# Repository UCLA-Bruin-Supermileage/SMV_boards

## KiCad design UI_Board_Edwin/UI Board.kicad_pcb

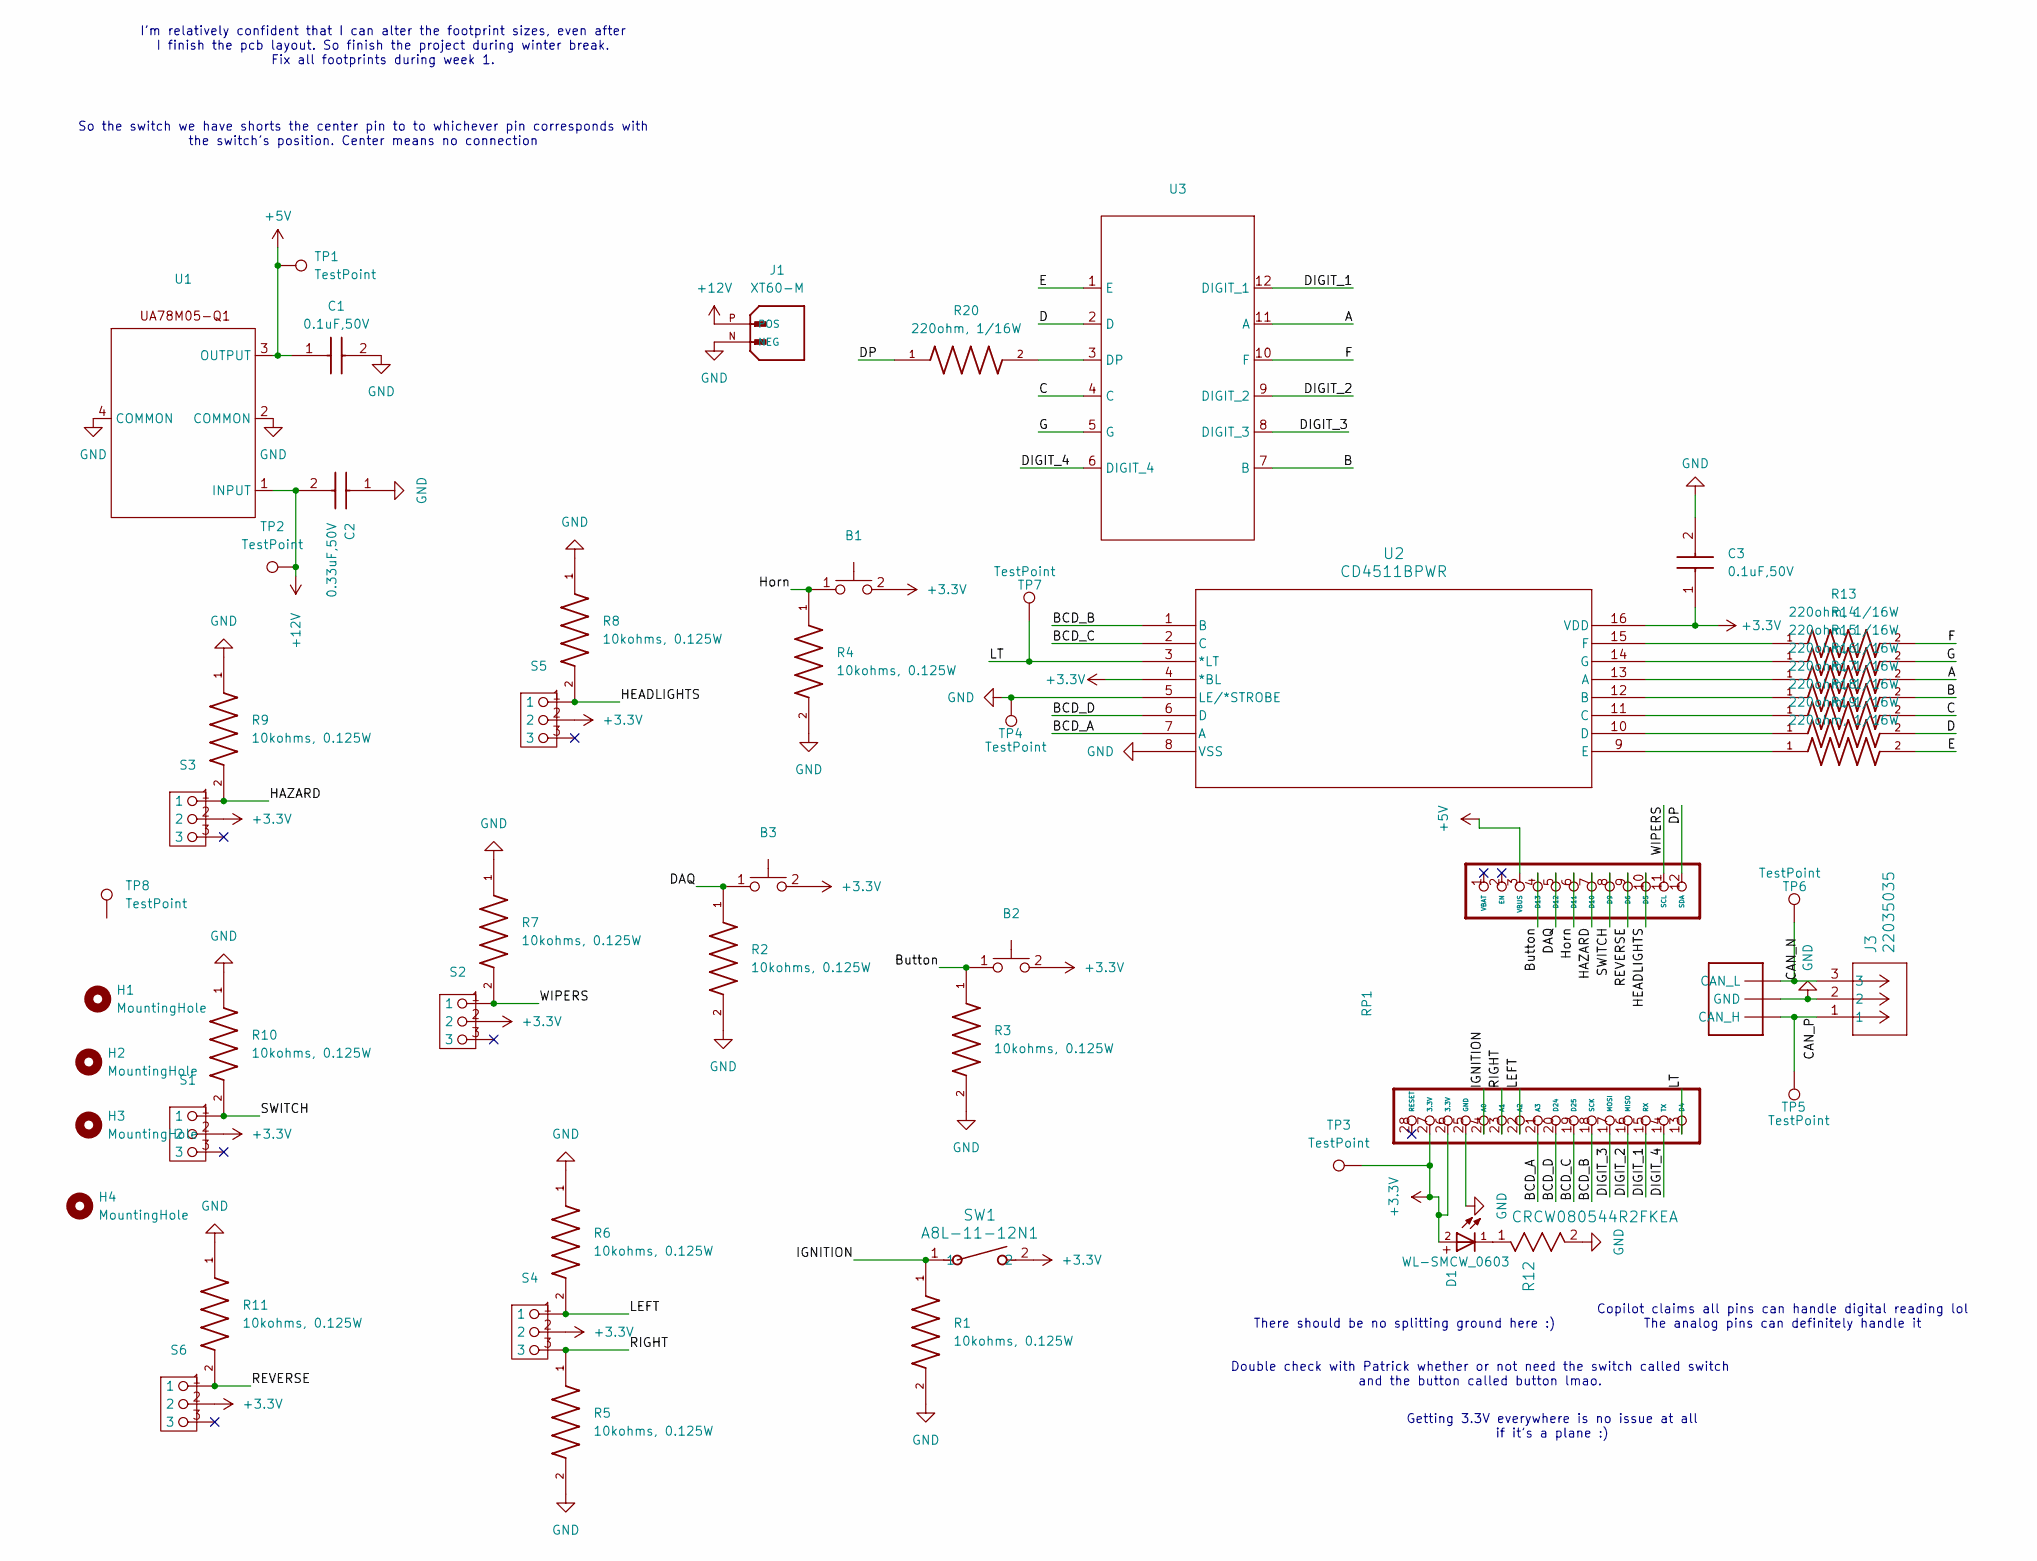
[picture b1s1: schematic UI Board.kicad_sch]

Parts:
B1, B2, B3: Twidec Button
C1, C3: 0.1uF,50V; Cap0805; Manufacturer_Part_Number C0805C104K5RACTU; Mouser Part Number 80-C0805C104K5R
C2: 0.33uF,50V; Cap0805; Manufacturer_Part_Number C0805C334K5RACTU; Mouser Part Number 80-C0805C334K5R
D1: WL-SMCW_0603; WL-SMCW_0603(diode)
H1, H2, H3, H4: MountingHole; MountingHole_3.2mm_M3
J1: XT60-M; AMASS_XT60-M; PARTREV V1.2
J3: 22035035; 3pin_CON_22035035_MOL
R1, R2, R3, R4, R5, R6, R7, R8, R9, R10, R11: 10kohms, 0.125W; 0805RESC2012X60N
R12: CRCW080544R2FKEA; 0805RESC2012X60N
R13, R14, R15, R16, R17, R18, R19, R20: 220ohm, 1/16W; RESC1005X35N
RP1: RP2040
S1, S2, S3, S4, S5, S6: Switches
SW1: A8L-11-12N1; SW_A8L-11_OMR
TP1, TP2, TP3, TP4, TP5, TP6, TP7: TestPoint; TestPoint_Pad_2.5x2.5mm
TP8: TestPoint; SEM_logo
U1: DCY4_TEX
U2: CD4511BPWR
U3: Seven_Seg_display

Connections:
+3.3V: B1.2, B2.2, B3.2, C3.1, D1.2, RP1.26 (3.3V), RP1.27 (3.3V), S1.2, S2.2, S3.2, S4.2, S5.2, S6.2, SW1.2, TP3.1, U2.4 (*BL), U2.16 (VDD)
+5V: C1.1, RP1.3 (VBUS), TP1.1, U1.3 (OUTPUT)
+12V: C2.2, J1.P (POS), TP2.1, U1.1 (INPUT)
/A: R15.2, U3.11 (A)
/B: R16.2, U3.7 (B)
/BCD_A: RP1.21 (A3), U2.7 (A)
/BCD_B: RP1.18 (SCK), U2.1 (B)
/BCD_C: RP1.19 (D25), U2.2 (C)
/BCD_D: RP1.20 (D24), U2.6 (D)
/Button: B2.1, R3.1, RP1.4 (D13)
/C: R17.2, U3.4 (C)
/CAN_N: J3.3, RP1.29 (CAN_L), TP6.1
/CAN_P: J3.1, RP1.31 (CAN_H), TP5.1
/D: R18.2, U3.2 (D)
/DAQ: B3.1, R2.1, RP1.5 (D12)
/DIGIT_1: RP1.15 (RX), U3.12 (DIGIT_1)
/DIGIT_2: RP1.16 (MISO), U3.9 (DIGIT_2)
/DIGIT_3: RP1.17 (MOSI), U3.8 (DIGIT_3)
/DIGIT_4: RP1.14 (TX), U3.6 (DIGIT_4)
/DP: R20.1, RP1.12 (SDA)
/E: R19.2, U3.1 (E)
/F: R13.2, U3.10 (F)
/G: R14.2, U3.5 (G)
/HAZARD: R9.2, RP1.7 (D10), S3.1
/HEADLIGHTS: R8.2, RP1.10 (D5), S5.1
/Horn: B1.1, R4.1, RP1.6 (D11)
/IGNITION: R1.1, RP1.24 (A0), SW1.1
/LEFT: R6.2, RP1.22 (A2), S4.1
/LT: RP1.13 (D4), TP7.1, U2.3 (*LT)
/REVERSE: R11.2, RP1.9 (D6), S6.1
/RIGHT: R5.1, RP1.23 (A1), S4.3
/SWITCH: R10.2, RP1.8 (D9), S1.1
/WIPERS: R7.2, RP1.11 (SCL), S2.1
GND: C1.2, C2.1, C3.2, J1.N (NEG), J3.2, R1.2, R2.2, R3.2, R4.2, R5.2, R6.1, R7.1, R8.1, R9.1, R10.1, R11.1, R12.2, RP1.25 (GND), RP1.30 (GND), TP4.1, U1.2 (COMMON), U1.4 (COMMON), U2.5 (LE/*STROBE), U2.8 (VSS)
unnamed: D1.1, R12.1
unnamed: R15.1, U2.13 (A)
unnamed: R16.1, U2.12 (B)
unnamed: R17.1, U2.11 (C)
unnamed: R18.1, U2.10 (D)
unnamed: R19.1, U2.9 (E)
unnamed: R13.1, U2.15 (F)
unnamed: R14.1, U2.14 (G)
unnamed: R20.2, U3.3 (DP)

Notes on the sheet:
Getting 3.3V everywhere is no issue at all if it's a plane :)
I'm relatively confident that I can alter the footprint sizes, even after I finish the pcb layout. So finish the project during winter break. Fix all footprints during week 1.
There should be no splitting ground here :)
Copilot claims all pins can handle digital reading lol The analog pins can definitely handle it
Double check with Patrick whether or not need the switch called switch and the button called button lmao.
So the switch we have shorts the center pin to to whichever pin corresponds with the switch's position. Center means no connection

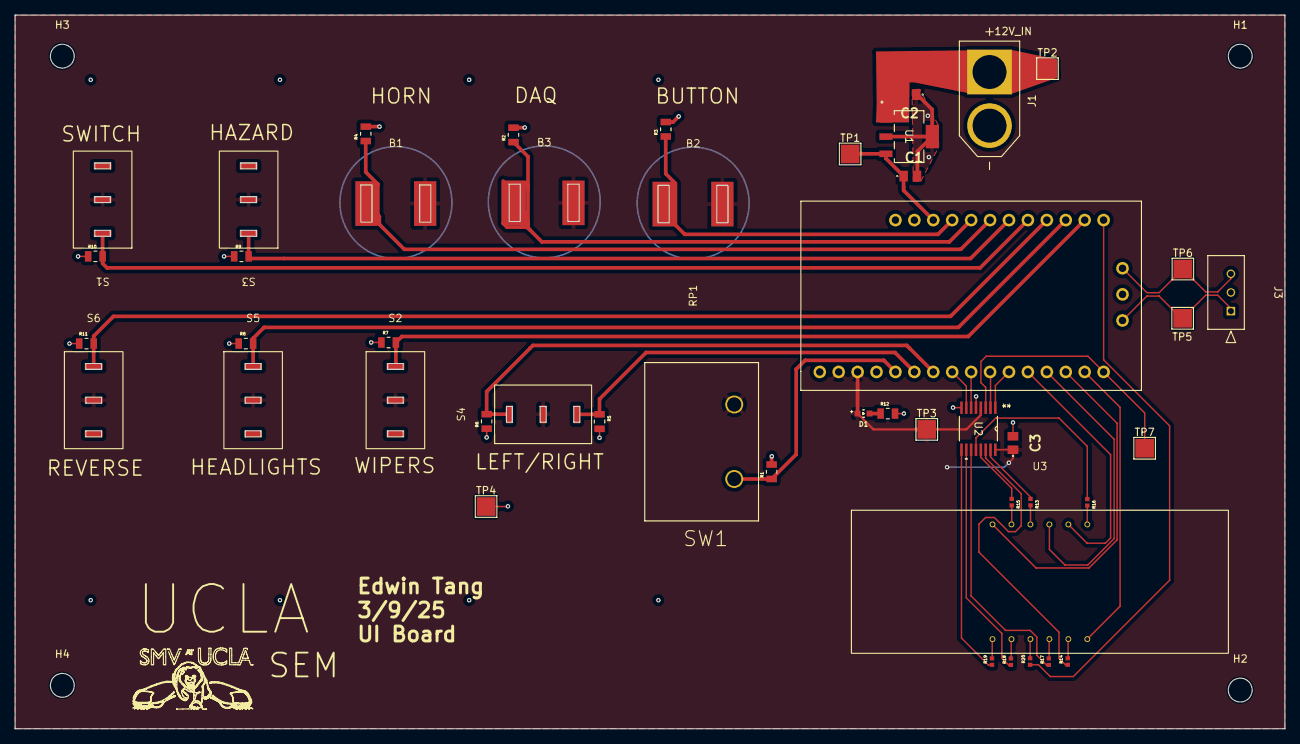
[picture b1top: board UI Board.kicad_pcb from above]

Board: 2 copper layers, 170.4 x 95.8 mm, 53 parts (0 on the bottom side), 43 nets.

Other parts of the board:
U1#2: UA78M05-Q1

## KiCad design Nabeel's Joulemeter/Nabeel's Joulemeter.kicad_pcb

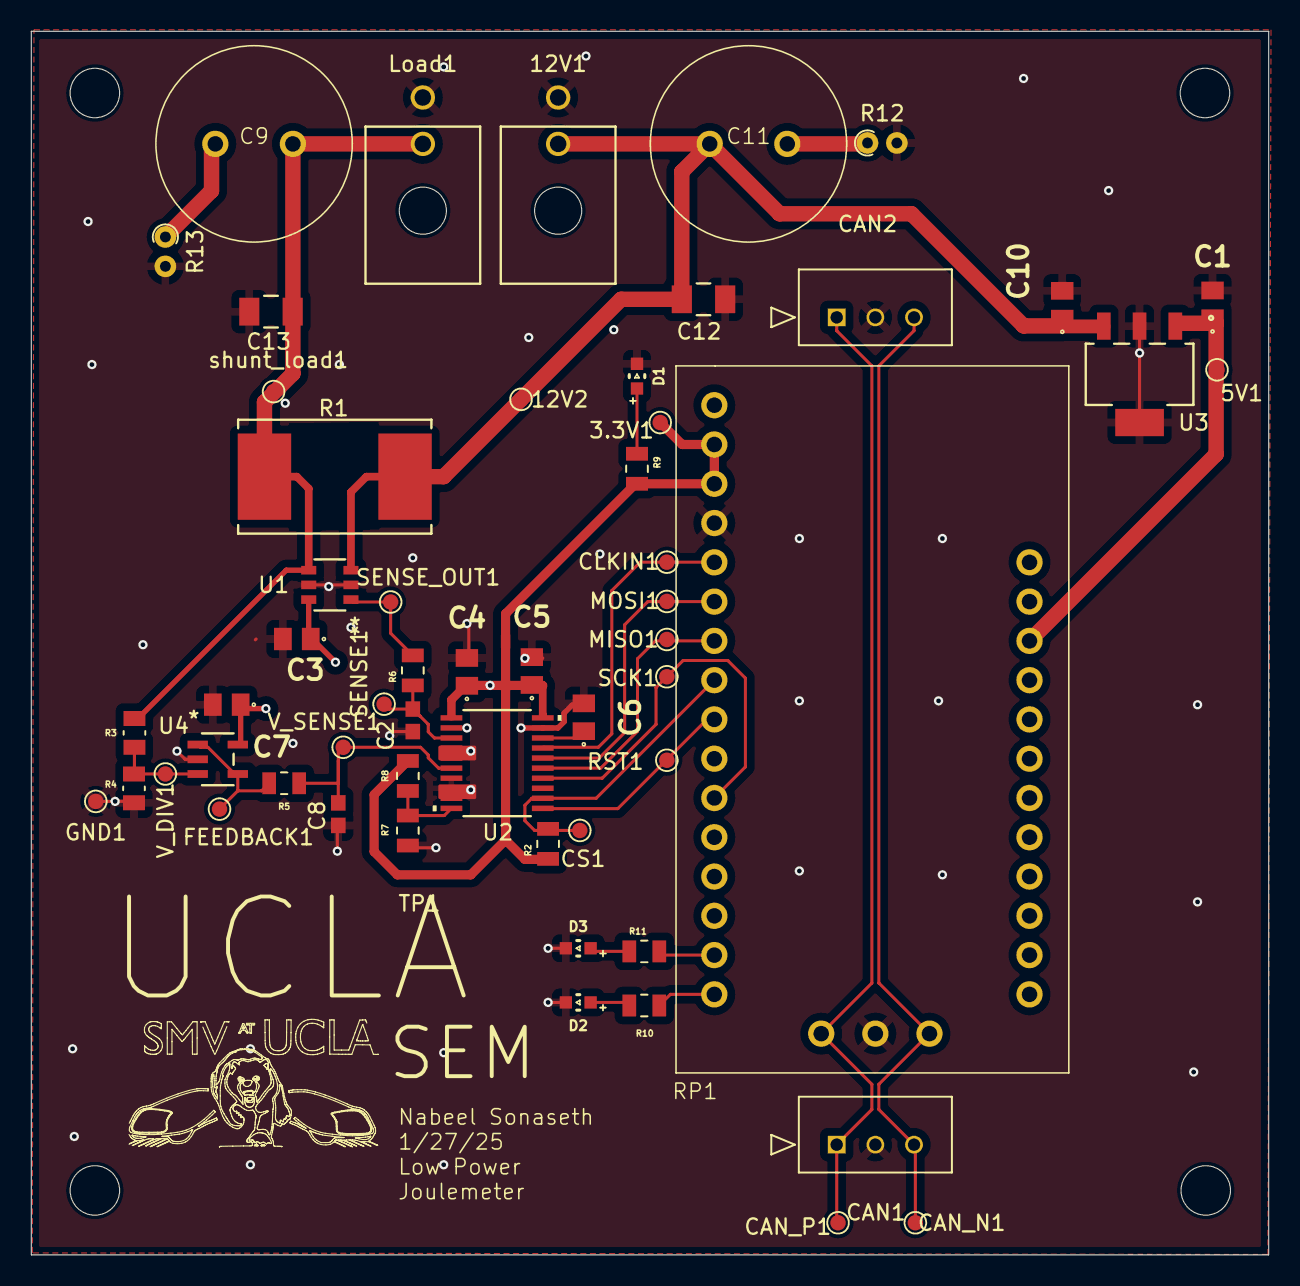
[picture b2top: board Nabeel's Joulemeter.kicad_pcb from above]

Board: 2 copper layers, 80.0 x 79.1 mm, 61 parts (0 on the bottom side), 25 nets.

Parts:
3.3V1, 5V1, 12V2: TestPoint; TestPoint_Pad_D1.0mm
12V1: 430450200; CONN_SD-43045-001_02_MOL
C1, C3, C7: 0.1uF,50V; Cap0805
C2, C8: 4.7nF; CAPC17595_87N_KEM
C4, C5: 1uF,50V; Cap0805
C6: 220nF, 16V; Cap0805
C9, C11: 470uF, 63V; Big_Chunky_Cap
C10: 0.47uF, 50V; Cap0805
C12, C13: 4.7uF, 100V; CAPC340180_180N_KEM
CAN1, CAN2: 22035035; 3pin_CON_22035035_MOL
CAN_N1: TestPoint; TestPoint_Pad_D1.0mm
CAN_P1: TestPoint; TestPoint_Pad_D1.0mm
CLKIN1: TestPoint; TestPoint_Pad_D1.0mm
CS1: TestPoint; TestPoint_Pad_D1.0mm
D1, D2, D3: WL-SMCW_0603; WL-SMCW_0603(diode)
FEEDBACK1: TestPoint; TestPoint_Pad_D1.0mm
GND1: TestPoint; TestPoint_Pad_D1.0mm
H1, H2, H3, H4: MountingHole; MountingHole_3.2mm_M3
Load1: 430450200; CONN_SD-43045-001_02_MOL
MISO1: TestPoint; TestPoint_Pad_D1.0mm
MOSI1: TestPoint; TestPoint_Pad_D1.0mm
R1: WSR5R0100FEA, 10mOhms; WSR
R2: 10kohms, 0.5W; 0805RESC2012X60N
R3: 51kohms; RESC2012X55N
R4: 10kohms; RESC2012X55N
R5, R6: 49.9ohms, 0.125W; 0805RESC2012X60N
R7, R8: 10kohms, 0.125W; 0805RESC2012X60N
R9, R10, R11: 150Ω, 0.125W; 0805RESC2012X60N
R12, R13: R_US; R_Axial_DIN0204_L3.6mm_D1.6mm_P1.90mm_Vertical
RP1: RP2040
RST1: TestPoint; TestPoint_Pad_D1.0mm
SCK1: TestPoint; TestPoint_Pad_D1.0mm
SENSE1: TestPoint; TestPoint_Pad_D1.0mm
SENSE_OUT1: TestPoint; TestPoint_Pad_D1.0mm
TP1: TestPoint; SEM_logo
U1: INA181A1QDBVRQ1; SOIC_DBVRQ1_TEX
U2: PADS131M04QPWRQ1; TSSOP20_PW_TEX
U3: UA78M05QDCYRG4Q1; DCY4_TEX
U4: MCP6286T-E/OT; SOT-23-5_MC_MCH
V_DIV1: TestPoint; TestPoint_Pad_D1.0mm
V_SENSE1: TestPoint; TestPoint_Pad_D1.0mm
shunt_load1: TestPoint; TestPoint_Pad_D1.0mm

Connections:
+3.3V: 3.3V1.1, C3.1, C4.1, C5.1, C7.1, R2.1, R8.1, R9.2, RP1.26 (3.3V), RP1.27 (3.3V), U1.6, U2.1 (AVDD), U2.20 (DVDD), U4.5 (VDD)
+5V: 5V1.1, C1.1, RP1.3 (VBUS), U3.1 (OUTPUT)
+12V: 12V1.1, 12V2.1, C10.1, C12.1, R1.1, U1.3, U3.3 (INPUT)
/AMPLIFIED_VOLTAGE: C2.2, R6.1, SENSE1.1, U2.3 (AIN0P)
/CAN_N: CAN1.3, CAN2.3, CAN_N1.1, RP1.29 (CAN_L)
/CAN_P: CAN1.1, CAN2.1, CAN_P1.1, RP1.31 (CAN_H)
/CS: CS1.1, R2.2, RP1.21 (A3), U2.12 (CS)
/DIVIDED_VOLTAGE: C8.2, R5.1, U2.6 (AIN1P), V_SENSE1.1
/FEEDBACK: FEEDBACK1.1, R5.2, U4.1 (VOUT), U4.4 (VIN-)
/GPIO_CLKIN: CLKIN1.1, RP1.24 (A0), U2.17 (CLKIN)
/GPIO_RESET: RP1.20 (D24), RST1.1, U2.11 (SYNC/RESET)
/MISO: MISO1.1, RP1.22 (A2), U2.15 (DOUT)
/MOSI: MOSI1.1, RP1.23 (A1), U2.16 (DIN)
/SCK: RP1.18 (SCK), SCK1.1, U2.14 (SCLK)
/SHUNT_TO_LOAD: C13.1, Load1.1, R1.2, R3.2, U1.4, shunt_load1.1
GND: 12V1.2, C1.2, C2.1, C3.2, C4.2, C5.2, C6.2, C7.2, C8.1, C10.2, C12.2, C13.2, CAN1.2, CAN2.2, D1.1, D2.1, D3.1, GND1.1, Load1.2, R4.1, R7.2, R12.2, R13.2, RP1.25 (GND), RP1.30 (GND), U1.2, U1.5, U2.2 (AGND), U2.4 (AIN0N), U2.5 (AIN1N), U2.7 (AIN2P), U2.8 (AIN2N), U2.9 (AIN3N), U2.19 (DGND), U3.2 (GND), U3.4 (GND), U4.2 (VSS)
unnamed: D1.2, R9.1
unnamed: D2.2, R10.1
unnamed: D3.2, R11.1
unnamed: R6.2, SENSE_OUT1.1, U1.1
unnamed: R10.2, RP1.13 (D4)
unnamed: R11.2, RP1.14 (TX)
unnamed: R7.1, R8.2, U2.10 (AIN3P)
unnamed: C6.1, U2.18 (CAP)
unnamed: R3.1, R4.2, U4.3 (VIN+), V_DIV1.1

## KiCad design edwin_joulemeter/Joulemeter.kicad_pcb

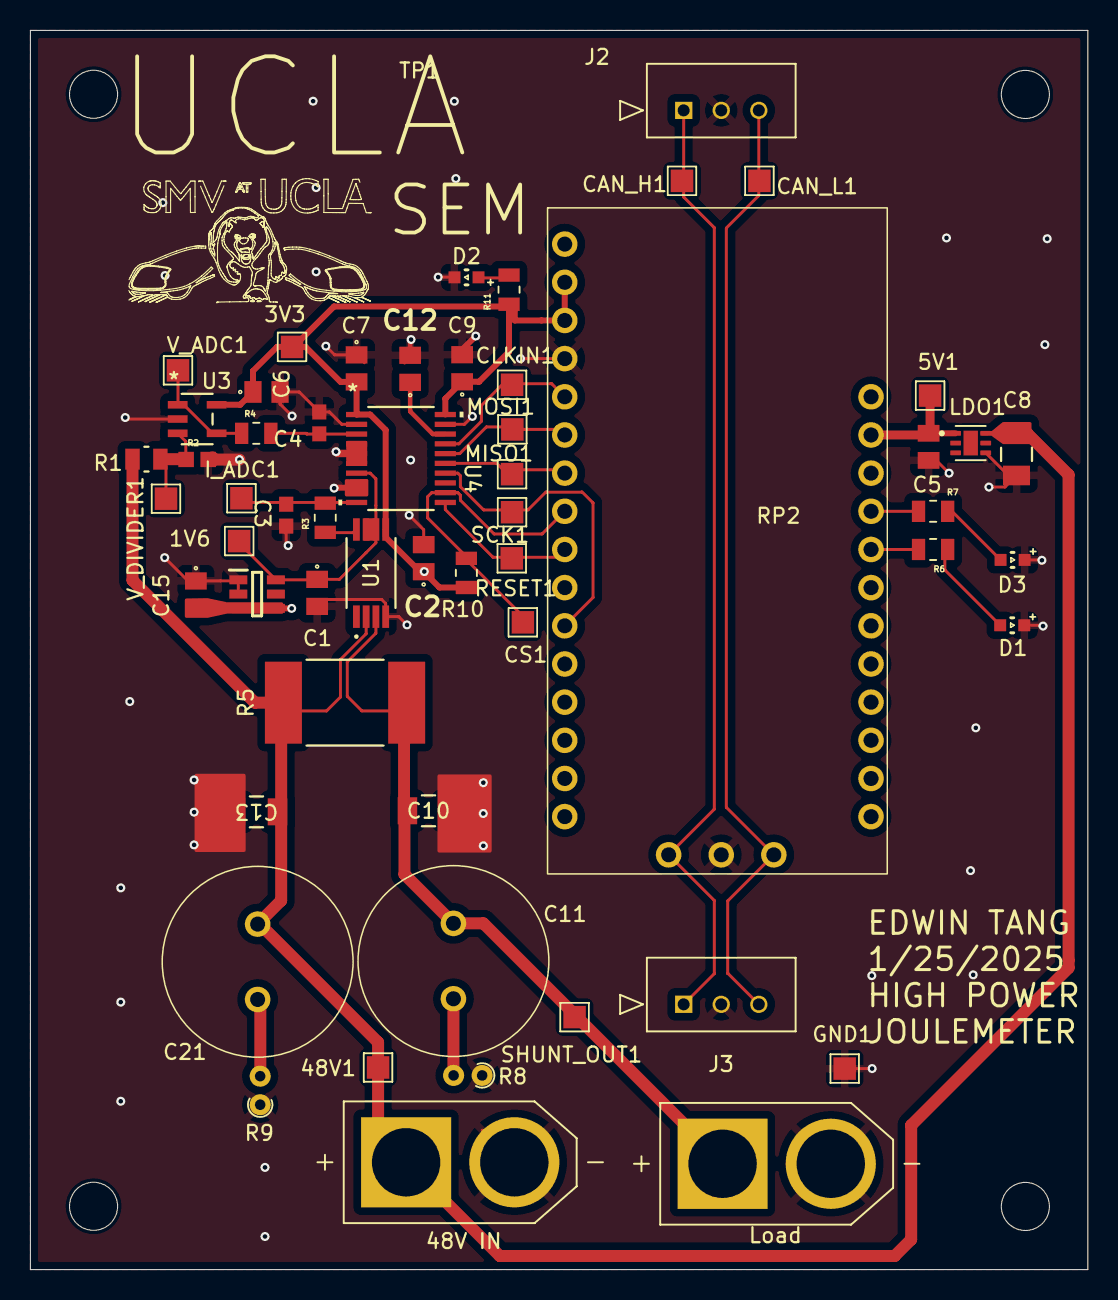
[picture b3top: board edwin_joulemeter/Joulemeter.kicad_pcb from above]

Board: 2 copper layers, 70.4 x 82.5 mm, 57 parts (0 on the bottom side), 25 nets.

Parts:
1V6, 3V3, 5V1, 48V1: TestPoint; TestPoint_Pad_1.5x1.5mm
C1, C4: 1uF,50V; Cap0805
C2: 0.1uF, 16V; Cap0805
C3, C6: 4.7nF,16V; CAPC17595_87N_KEM
C5: 10uF, 10V; CAP_8PACTU
C7, C9: 1uF,16V; Cap0805
C8: 1uF, 100V; CAPC340180_180N_KEM
C10, C13: 4.7uF, 100V; CAPC340180_180N_KEM
C11, C21: 470uF, 63V; Big_Chunky_Cap
C12: 220nF, 6.3V; Cap0805
C15: 0.1uF,50V; Cap0805
CAN_H1: TestPoint; TestPoint_Pad_1.5x1.5mm
CAN_L1: TestPoint; TestPoint_Pad_1.5x1.5mm
CLKIN1: TestPoint; TestPoint_Pad_1.5x1.5mm
CS1: TestPoint; TestPoint_Pad_1.5x1.5mm
D1, D2, D3: WL-SMCW_0603; WL-SMCW_0603(diode)
GND1: TestPoint; TestPoint_Pad_1.5x1.5mm
I_ADC1: TestPoint; TestPoint_Pad_1.5x1.5mm
J1, J4: XT60-M; AMASS_XT60-M
J2, J3: 22035035; 3pin_CON_22035035_MOL
LDO1: U-DFN2020-6 (Type C)
MISO1: TestPoint; TestPoint_Pad_1.5x1.5mm
MOSI1: TestPoint; TestPoint_Pad_1.5x1.5mm
R1: 500 kOHM, 0.26 W; RES_TNPW0805_VIS
R2: 20kohms, 0.13W; 0603_resistors
R3, R4: 49.9ohm, 0.1W; 0805RESC2012X60N
R5: 0.0005ohm, 3W; RES_PU3921_.5mOHM_YAG
R6, R7, R11: 150ohm, 0.1W; 0805RESC2012X60N
R8, R9: R_US; R_Axial_DIN0204_L3.6mm_D1.6mm_P1.90mm_Vertical
R10: 10kohms, 0.125W; 0805RESC2012X60N
REF35160QDBVR1: SOT95P280X145-6N
RESET1: TestPoint; TestPoint_Pad_1.5x1.5mm
RP2: RP2040
SCK1: TestPoint; TestPoint_Pad_1.5x1.5mm
SHUNT_OUT1: TestPoint; TestPoint_Pad_1.5x1.5mm
TP1: TestPoint; SEM_logo
U1: INA240A3PWR; PW0008A_N_TEX
U3: MCP6286T-E/OT; SOT-23-5_MC_MCH
U4: PADS131M04QPWRQ1; TSSOP20_PW_TEX
V_ADC1: TestPoint; TestPoint_Pad_1.5x1.5mm
V_DIVIDER1: TestPoint; TestPoint_Pad_1.5x1.5mm

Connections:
+1V6: 1V6.1, C1.1, REF35160QDBVR1.6 (VREF), U1.6 (REF2), U1.7 (REF1), U4.7 (AIN2P)
+3V3: 3V3.1, C2.1, C4.1, C7.2, C9.1, C15.2, R10.2, R11.1, REF35160QDBVR1.3 (EN), REF35160QDBVR1.4 (VIN), RP2.26 (3.3V), RP2.27 (3.3V), U1.5 (VS), U3.5 (VDD), U4.1 (AVDD), U4.20 (DVDD)
+5V: 5V1.1, C5.2, LDO1.1 (VOUT), RP2.2 (EN)
+48V: 48V1.1, C8.1, C13.1, J1.P (POS), LDO1.6 (VIN), R1.1, R5.1, U1.2 (IN+)
/CAN_H: CAN_H1.1, J2.1, J3.1, RP2.31 (CAN_H)
/CAN_L: CAN_L1.1, J2.3, J3.3, RP2.29 (CAN_L)
/CS: CS1.1, R10.1, RP2.21 (A3), U4.12 (CS)
/GPIO_CLKIN: CLKIN1.1, RP2.24 (A0), U4.17 (CLKIN)
/GPIO_RESET: RESET1.1, RP2.20 (D24), U4.11 (SYNC/RESET)
/I_ADC: C3.1, I_ADC1.1, R3.2, U4.10 (AIN3P)
/MISO: MISO1.1, RP2.22 (A2), U4.15 (DOUT)
/MOSI: MOSI1.1, RP2.23 (A1), U4.16 (DIN)
/OP_AMP: R4.1, U3.1 (VOUT), U3.4 (VIN-), V_ADC1.1
/SCK: RP2.18 (SCK), SCK1.1, U4.14 (SCLK)
/SHUNT_OUT: C10.1, J4.P (POS), R5.2, SHUNT_OUT1.1, U1.3 (IN-)
/V_ADC: C6.1, R4.2, U4.3 (AIN0P)
GND: C1.2, C2.2, C3.2, C4.2, C5.1, C6.2, C7.1, C8.2, C9.2, C10.2, C12.2, C13.2, C15.1, D1.1, D2.1, D3.1, GND1.1, J1.N (NEG), J2.2, J3.2, J4.N (NEG), LDO1.4 (GND), R2.2, R8.1, R9.1, REF35160QDBVR1.1 (GND), REF35160QDBVR1.2 (GND), RP2.25 (GND), RP2.30 (GND), U1.4 (GND), U3.2 (VSS), U4.2 (AGND), U4.4 (AIN0N), U4.5 (AIN1N), U4.6 (AIN1P), U4.8 (AIN2N), U4.9 (AIN3N), U4.19 (DGND)
unnamed: D1.2, R6.1
unnamed: D2.2, R11.2
unnamed: D3.2, R7.2
unnamed: R6.2, RP2.5 (D12)
unnamed: R7.1, RP2.4 (D13)
unnamed: R3.1, U1.8 (OUT)
unnamed: R1.2, R2.1, U3.3 (VIN+), V_DIVIDER1.1
unnamed: C12.1, U4.18 (CAP)

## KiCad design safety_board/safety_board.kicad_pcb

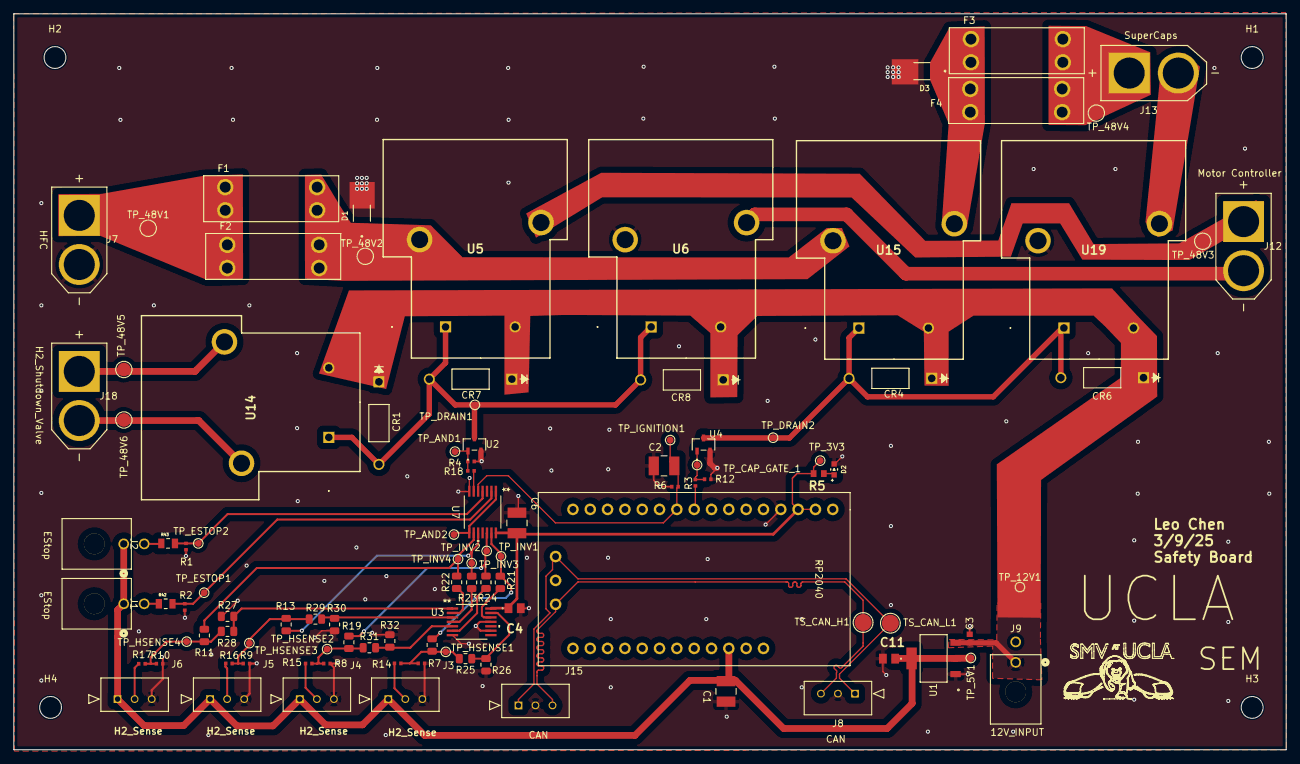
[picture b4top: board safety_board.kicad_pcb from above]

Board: 2 copper layers, 186.6 x 107.9 mm, 108 parts (0 on the bottom side), 48 nets.

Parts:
C1, C2, C6: 1 µF; CAPC340270_190N_KEM-M
C3: C0603C474K4RACTU; CAPC17595_87N_KEM-L
C4: 0.1uF,50V; Cap0805
C11: Cap0805
CR1, CR4, CR6, CR7, CR8: 1N4007-G; 1N4-G
D1, D3: SMA4S56AH; SODFL4725X110N
D2: WL-SMCW_0603; WL-SMCW_0603(diode)
F1, F2, F3, F4: 3557-2; FUSE_3557-2
H1, H2, H3, H4: MountingHole; MountingHole_3.2mm_M3
J1, J2, J9: 430450200; CONN_SD-43045-001_02_MOL
J3, J4, J5, J6, J8, J15: 22035035; 3pin_CON_22035035_MOL
J7, J12, J13, J18: XT60-M; AMASS_XT60-M
R1, R2, R4, R6, R7, R8, R9, R10, R12: 10k ohms; RES_CRCW_0402
R3, R14, R15, R16, R17, R18: 1.5k ohms; RES_CRCW_0402
R5: 150 ohm; RESC1608X50N
R11, R13, R19, R20, R21, R22, R23, R24, R25, R26, R27, R28, R29, R30, R31, R32: R; R_0805_2012Metric
R42, R43: 5k ohms; RESC2012X50N
RP2040: RP2040
TP1: TestPoint; SEM_logo
TP_3V3, TP_5V1, TP_12V1: TestPoint_Pad_D1.0mm
TP_48V1, TP_48V2, TP_48V3, TP_48V4, TP_48V5, TP_48V6: V_DIVIDED; TestPoint_Pad_D2.0mm
TP_AND1, TP_AND2: TestPoint; TestPoint_Pad_D1.0mm
TP_CAP_GATE_1: TestPoint; TestPoint_Pad_D1.0mm
TP_DRAIN1, TP_DRAIN2: TestPoint; TestPoint_Pad_D1.0mm
TP_ESTOP1, TP_ESTOP2: TestPoint; TestPoint_Pad_D1.0mm
TP_HSENSE1, TP_HSENSE2, TP_HSENSE3, TP_HSENSE4: TestPoint; TestPoint_Pad_D1.0mm
TP_IGNITION1: TestPoint; TestPoint_Pad_D1.0mm
TP_INV1, TP_INV2, TP_INV3, TP_INV4: TestPoint; TestPoint_Pad_D1.0mm
TS_CAN_H1: TestPoint_Pad_D2.5mm
TS_CAN_L1: TestPoint_Pad_D2.5mm
U1: LDL1117S50R; SOT223_STM
U2, U4: IRLML6344TRPBF; IRLML6344TRPBF_INF-L
U3: SN74AHCT14QPWRQ1; PW14
U5, U6, U14, U15, U19: J115F11AH12VDCS61.5U; J115F11AH12VDCS615U
U7: SN74HCS21QPWRQ1; TSSOP14_PW_TEX-M

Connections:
+3V3: C4.1, C6.1, R5.2, RP2040.26 (3.3V), RP2040.27 (3.3V), TP_3V3.1, U3.14 (VCC), U7.14 (VCC)
+5V: C1.1, C11.1, J1.1, J2.1, J3.1, J4.1, J5.1, J6.1, RP2040.3 (VBUS), TP_5V1.1, U1.2 (VOUT), U1.4 (VOUT)
+12V: C3.1, CR1.1, CR4.1, CR6.1, CR7.1, CR8.1, J9.1, TP_12V1.1, U1.3 (VIN), U5.2 (COIL_2), U6.2 (COIL_2), U14.2 (COIL_2), U15.2 (COIL_2), U19.2 (COIL_2)
/CAN_N: J8.3, J15.3, RP2040.29 (CAN_L), TS_CAN_L1.1
/CAN_P: J8.1, J15.1, RP2040.31 (CAN_H), TS_CAN_H1.1
/DRAIN: CR1.2, CR7.2, CR8.2, TP_DRAIN1.1, U2.3 (D), U5.1 (COIL_1), U6.1 (COIL_1), U14.1 (COIL_1)
/DRAIN2: CR4.2, CR6.2, TP_DRAIN2.1, U4.3 (D), U15.1 (COIL_1), U19.1 (COIL_1)
/ESTOP1: R2.1, R42.2, TP_ESTOP1.1, U7.2 (1B)
/ESTOP2: R1.1, R43.2, TP_ESTOP2.1, U7.4 (1C)
/HSENSE: R7.1, R14.2, R20.2, R25.2, TP_HSENSE1.1
/HSENSE_2: R8.1, R15.2, R19.2, R31.1, TP_HSENSE2.1
/HSENSE_3: R9.1, R13.2, R16.2, R29.1, TP_HSENSE3.1
/HSENSE_4: R10.1, R11.2, R17.2, R28.1, TP_HSENSE4.1
/IGNITION: C2.1, R6.1, RP2040.19 (D25), TP_IGNITION1.1, U7.5 (1D)
/INVERT: R20.1, R21.2, TP_INV1.1, U7.13 (2D)
/INVERT2: R19.1, R24.1, TP_INV2.1, U7.12 (2C)
/INVERT3: R13.1, R23.1, TP_INV3.1, U7.10 (2B)
/INVERT4: R11.1, R22.1, TP_INV4.1, U7.9 (2A)
GND: C1.2, C2.2, C3.2, C4.2, C6.2, C11.2, D1.A, D2.1, D3.A, J3.3, J4.3, J5.3, J6.3, J7.N (NEG), J8.2, J9.2, J15.2, R1.2, R2.2, R4.1, R6.2, R7.2, R8.2, R9.2, R10.2, R12.1, R26.1, R27.1, R30.1, R32.1, RP2040.25 (GND), RP2040.30 (GND), U1.1 (GND), U2.2 (S), U3.7 (GND), U3.9 (4A), U3.11 (5A), U4.2 (S), U6.4 (COM), U7.7 (GND), U19.4 (COM)
unnamed: D2.2, R5.1
unnamed: J1.2, R42.1
unnamed: J2.2, R43.1
unnamed: J3.2, R14.1
unnamed: J4.2, R15.1
unnamed: J5.2, R16.1
unnamed: J6.2, R17.1
unnamed: F1.1_1, F2.1_1, J7.P (POS), TP_48V1.1
unnamed: J12.N (NEG), U6.3 (NO)
unnamed: J12.P (POS), TP_48V3.1, U5.3 (NO)
unnamed: J13.N (NEG), U19.3 (NO)
unnamed: F3.2_1, F4.2_1, J13.P (POS), TP_48V4.1
unnamed: J18.N (NEG), TP_48V6.1, U14.4 (COM)
unnamed: J18.P (POS), TP_48V5.1, U14.3 (NO)
unnamed: R3.1, RP2040.20 (D24)
unnamed: R4.2, R18.1, TP_AND1.1, U2.1 (G)
unnamed: R27.2, R28.2, U3.1 (1A)
unnamed: R22.2, U3.2 (1Y)
unnamed: R29.2, R30.2, U3.3 (2A)
unnamed: R23.2, U3.4 (2Y)
unnamed: R31.2, R32.2, U3.5 (3A)
unnamed: R24.2, U3.6 (3Y)
unnamed: R25.1, R26.2, U3.13 (6A)
unnamed: R21.1, U3.12 (6Y)
unnamed: R3.2, R12.2, TP_CAP_GATE_1.1, U4.1 (G)
unnamed: TP_AND2.1, U7.1 (1A), U7.8 (2Y)
unnamed: R18.2, U7.6 (1Y)
unnamed: D1.C, F1.2_1, F2.2_1, TP_48V2.1, U5.4 (COM), U15.4 (COM)
unnamed: D3.C, F3.1_1, F4.1_1, U15.3 (NO)

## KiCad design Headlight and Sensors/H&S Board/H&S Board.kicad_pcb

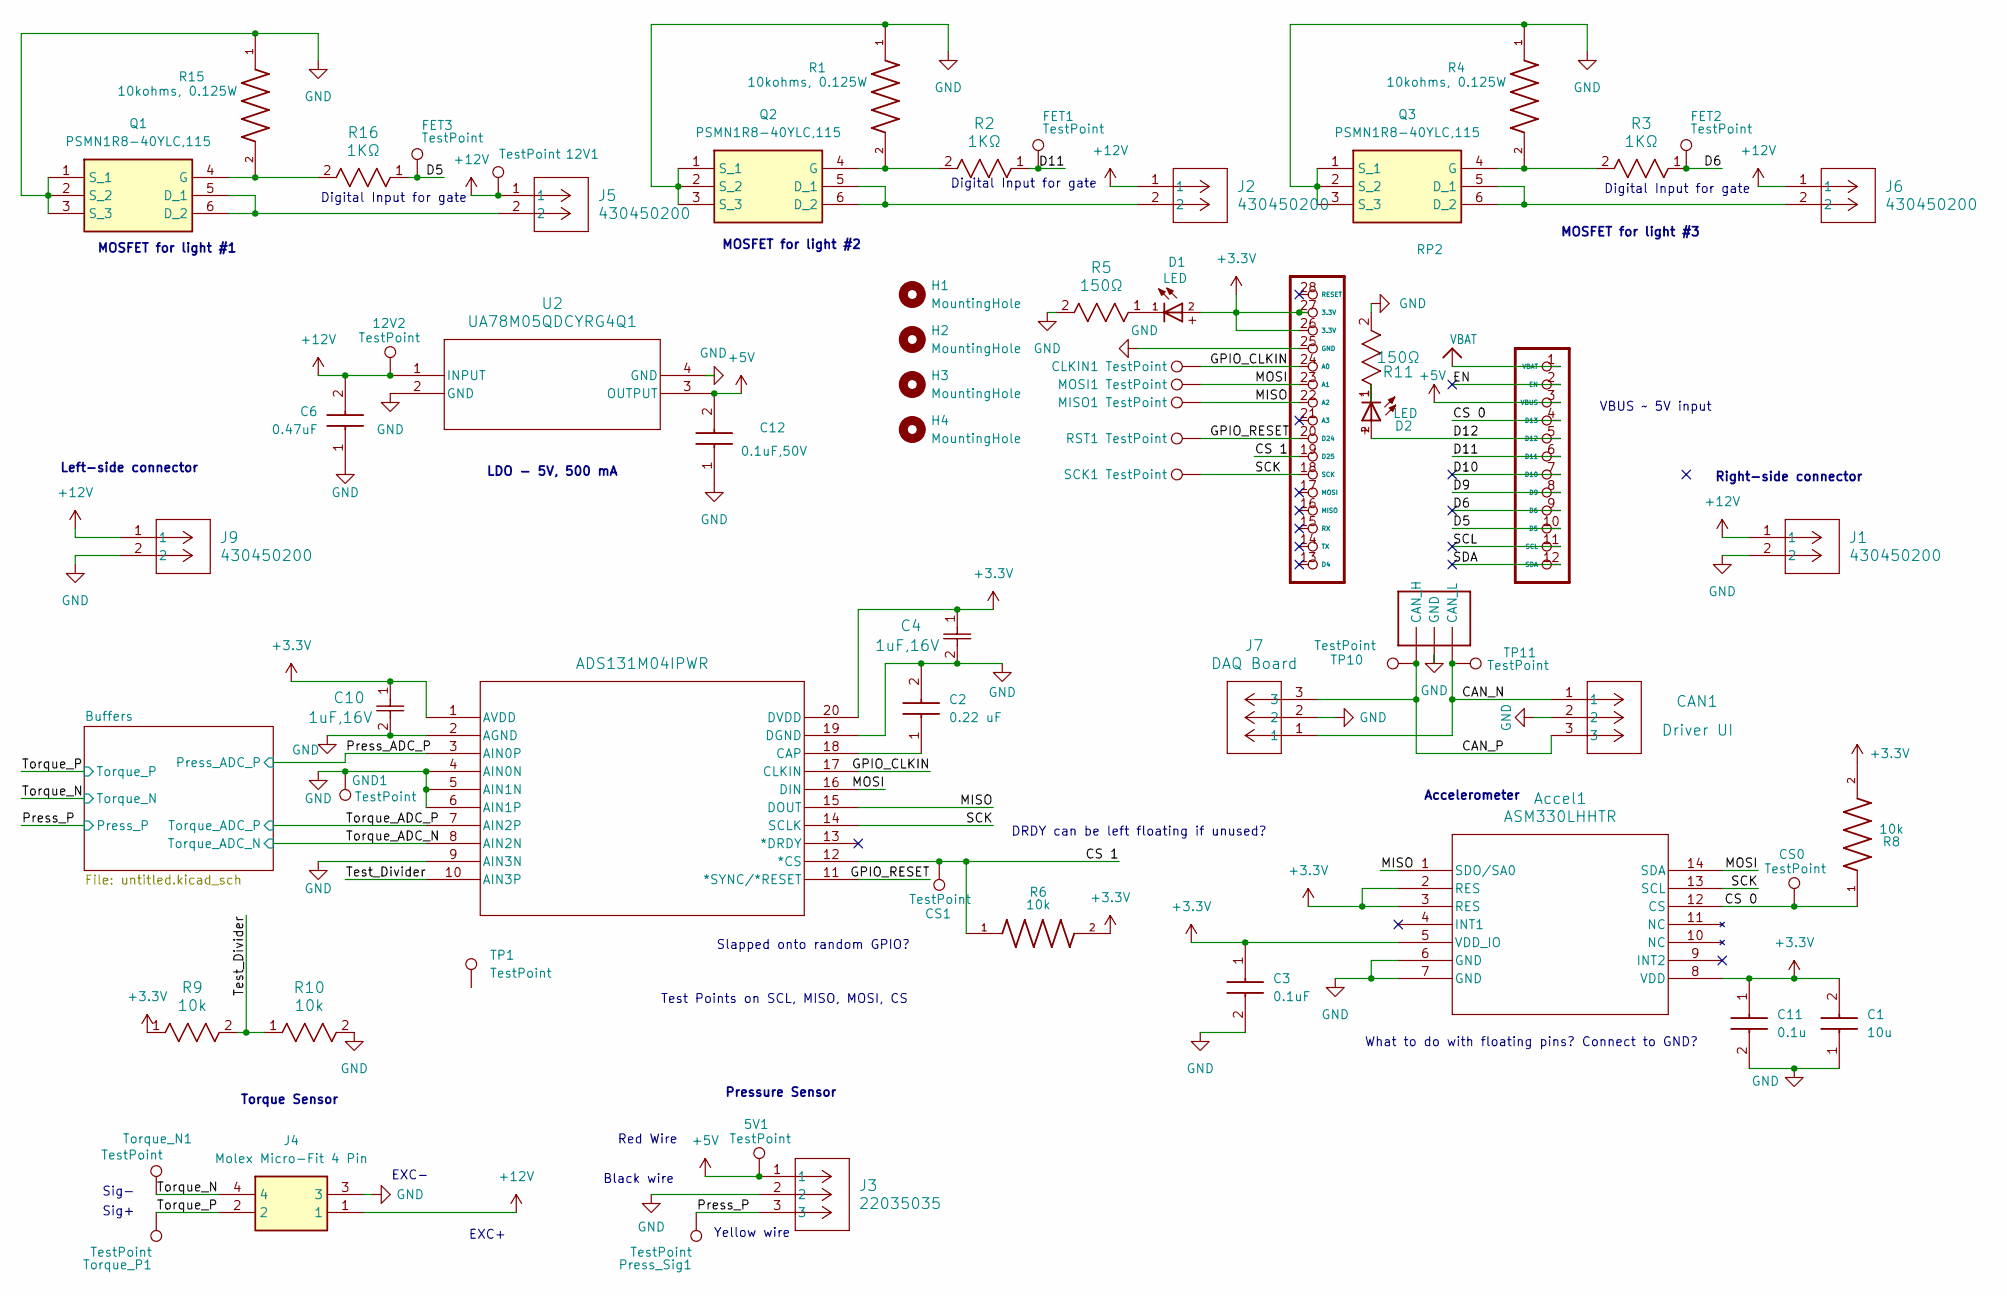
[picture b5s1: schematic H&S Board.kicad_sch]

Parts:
5V1, 12V2: TestPoint; TestPoint_Pad_D1.0mm
12V1: TestPoint; TestPoint_Pad_D1.5mm
Accel1: ASM330LHHTR; LGA-14L_2P5X3X0P83_STM
C1: 10u; Cap0805; Manufacturer_Part_Number C0805C106K8RACTU; Mouser Part Number 80-C0805C106K8R
C2: 0.22 uF; Cap0805; Manufacturer_Part_Number C0805C224K3RACTU; Mouser Part Number 80-C0805C224K3R
C3: 0.1uF; Cap0805; Manufacturer_Part_Number C0805C104K5RACTU; Mouser Part Number 80-C0805C104K5R
C4, C10: 1uF,16V; Cap0805
C6: 0.47uF; Cap0805; Manufacturer_Part_Number C0805C475K4RACTU
C11: 0.1u; Cap0805; Manufacturer_Part_Number C0805C104K5RACTU; Mouser Part Number 80-C0805C104K5R
C12: 0.1uF,50V; Cap0805; Manufacturer_Part_Number C0805C104K5RACTU; Mouser Part Number 80-C0805C104K5R
CAN1: Driver UI; 3pin_CON_22035035_MOL
CLKIN1: TestPoint; TestPoint_Pad_D1.0mm
CS0, CS1: TestPoint; TestPoint_Pad_D1.0mm
D1, D2: LED; WL-SMCW_0603(diode)
FET1, FET2, FET3: TestPoint; TestPoint_Pad_D1.0mm
GND1: TestPoint; TestPoint_Pad_D1.0mm
H1, H2, H3, H4: MountingHole; MountingHole_3.2mm_M3
J1, J2, J5, J6, J9: 430450200; CONN_SD-43045-001_02_MOL
J3: 22035035; 3pin_CON_22035035_MOL
J4: Molex Micro-Fit 4 Pin; 4_pin0430450401; Manufacturer_Part_Number 0430450401
J7: DAQ Board; 3pin_CON_22035035_MOL
MISO1: TestPoint; TestPoint_Pad_D1.0mm
MOSI1: TestPoint; TestPoint_Pad_D1.0mm
Press_Sig1: TestPoint; TestPoint_Pad_D1.0mm
Q1, Q2, Q3: PSMN1R8-40YLC,115; PSMN1R840YLC115; Mouser Part Number 771-PSMN1R8-40YLC115
R1, R4, R15: 10kohms, 0.125W; 0805RESC2012X60N
R2, R3, R16: 1KΩ; 0805RESC2012X60N
R5, R11: 150Ω; 0805RESC2012X60N
R6, R8: 10k; 0805RESC2012X60N
R9, R10: 10k; RES_TNPW0402_VIS
RP2: RP2040
RST1: TestPoint; TestPoint_Pad_D1.0mm
SCK1: TestPoint; TestPoint_Pad_D1.0mm
TP1: TestPoint; SEM_logo
TP10, TP11: TestPoint; TestPoint_Pad_D1.0mm
Torque_N1: TestPoint; TestPoint_Pad_D1.0mm
Torque_P1: TestPoint; TestPoint_Pad_D1.0mm
U2: UA78M05QDCYRG4Q1; DCY4_TEX
U4: ADS131M04IPWR; PW20_TEX

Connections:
+3.3V: Accel1.2 (RES), Accel1.3 (RES), Accel1.5 (VDD_IO), Accel1.8 (VDD), C1.2, C3.1, C4.1, C10.1, C11.1, D1.2, R6.2, R8.2, R9.1, RP2.26 (3.3V), RP2.27 (3.3V), U4.1 (AVDD), U4.20 (DVDD); also elsewhere on the board
+5V: 5V1.1, C12.2, J3.1, RP2.3 (VBUS), U2.3 (OUTPUT)
+12V: 12V1.1, 12V2.1, C6.2, J1.1, J2.1, J4.1, J5.1, J6.1, J9.1, U2.1 (INPUT)
/CAN_N: CAN1.1, J7.1, RP2.29 (CAN_L), TP11.1
/CAN_P: CAN1.3, J7.3, RP2.31 (CAN_H), TP10.1
/CS 0: Accel1.12 (CS), CS0.1, R8.1, RP2.4 (D13)
/CS 1: CS1.1, R6.1, RP2.19 (D25), U4.12 (*CS)
/D5: FET3.1, R16.1, RP2.10 (D5)
/D6: FET2.1, R3.1, RP2.9 (D6)
/D9: RP2.8 (D9)
/D10: RP2.7 (D10)
/D11: FET1.1, R2.1, RP2.6 (D11)
/D12: D2.2, RP2.5 (D12)
/EN: RP2.2 (EN)
/GPIO_CLKIN: CLKIN1.1, RP2.24 (A0), U4.17 (CLKIN)
/GPIO_RESET: RP2.20 (D24), RST1.1, U4.11 (*SYNC/*RESET)
/MISO: Accel1.1 (SDO/SA0), MISO1.1, RP2.22 (A2), U4.15 (DOUT)
/MOSI: Accel1.14 (SDA), MOSI1.1, RP2.23 (A1), U4.16 (DIN)
/Press_ADC_P: U4.3 (AIN0P); also elsewhere on the board
/Press_P: J3.3, Press_Sig1.1; also elsewhere on the board
/SCK: Accel1.13 (SCL), RP2.18 (SCK), SCK1.1, U4.14 (SCLK)
/SCL: RP2.11 (SCL)
/SDA: RP2.12 (SDA)
/Test_Divider: R9.2, R10.1, U4.10 (AIN3P)
/Torque_ADC_N: U4.8 (AIN2N); also elsewhere on the board
/Torque_ADC_P: U4.7 (AIN2P); also elsewhere on the board
/Torque_N: J4.4, Torque_N1.1; also elsewhere on the board
/Torque_P: J4.2, Torque_P1.1; also elsewhere on the board
GND: Accel1.6 (GND), Accel1.7 (GND), C1.1, C2.2, C3.2, C4.2, C6.1, C10.2, C11.2, C12.1, CAN1.2, GND1.1, J1.2, J3.2, J4.3, J7.2, J9.2, Q1.1 (S_1), Q1.2 (S_2), Q1.3 (S_3), Q2.1 (S_1), Q2.2 (S_2), Q2.3 (S_3), Q3.1 (S_1), Q3.2 (S_2), Q3.3 (S_3), R1.1, R4.1, R5.2, R10.2, R11.2, R15.1, RP2.25 (GND), RP2.30 (GND), U2.2 (GND), U2.4 (GND), U4.2 (AGND), U4.4 (AIN0N), U4.5 (AIN1N), U4.6 (AIN1P), U4.9 (AIN3N), U4.19 (DGND); also elsewhere on the board
unnamed: D1.1, R5.1
unnamed: D2.1, R11.1
unnamed: J5.2, Q1.5 (D_1), Q1.6 (D_2)
unnamed: Q1.4 (G), R15.2, R16.2
unnamed: J2.2, Q2.5 (D_1), Q2.6 (D_2)
unnamed: Q2.4 (G), R1.2, R2.2
unnamed: J6.2, Q3.5 (D_1), Q3.6 (D_2)
unnamed: Q3.4 (G), R3.2, R4.2
unnamed: C2.1, U4.18 (CAP)
VBAT: RP2.1 (VBAT)

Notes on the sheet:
MOSFET for light #2
Torque Sensor
Black wire
Sig+
Red Wire
Digital Input for gate
Pressure Sensor
VBUS ~ 5V input
EXC-
Sig-
What to do with floating pins? Connect to GND?
Left-side connector
Right-side connector
Accelerometer
MOSFET for light #3
DRDY can be left floating if unused?
EXC+
LDO - 5V, 500 mA
Slapped onto random GPIO?
MOSFET for light #1
Yellow wire
Test Points on SCL, MISO, MOSI, CS
